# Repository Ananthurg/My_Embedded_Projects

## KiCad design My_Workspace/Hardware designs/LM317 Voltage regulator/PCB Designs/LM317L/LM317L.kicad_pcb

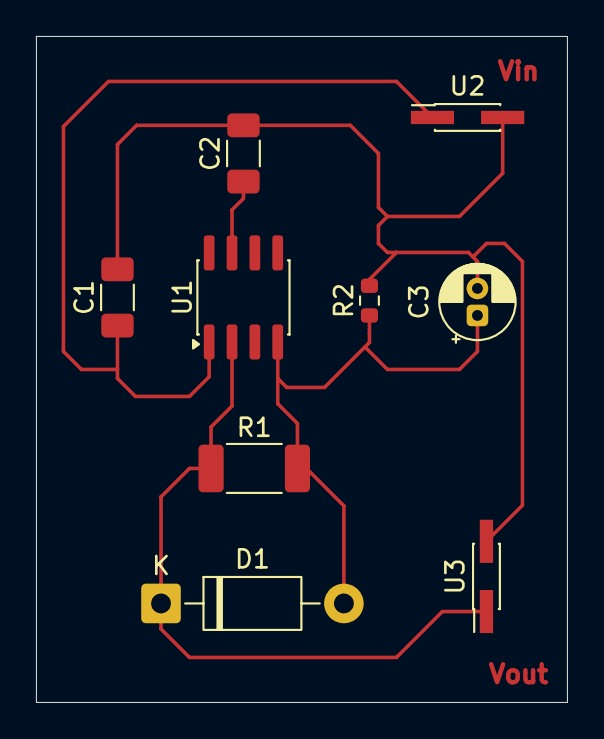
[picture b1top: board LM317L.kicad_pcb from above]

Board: 2 copper layers, 29.5 x 37.0 mm, 9 parts (0 on the bottom side), 4 nets.

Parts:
C1: 0.1uF; C_1206_3216Metric_Pad1.33x1.80mm_HandSolder
C2: 1uF; C_1206_3216Metric_Pad1.33x1.80mm_HandSolder
C3: 10uF; CP_Radial_D4.0mm_P1.50mm
D1: 1N4002; D_DO-41_SOD81_P10.16mm_Horizontal
R1: 470ohm; R_2010_5025Metric_Pad1.40x2.65mm_HandSolder
R2: 760ohm; R_0603_1608Metric
U1: LM317L_SO8; SOIC-8_3.9x4.9mm_P1.27mm
U2, U3: PinHeader_2x01_P1.27mm_Vertical_SMD

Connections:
+12V: C1.1, U1.1 (VI), U2.1
GND: C1.2, C2.2, C3.2, R2.2, U2.2, U3.2
unnamed: C3.1, D1.2 (A), R1.2, R2.1, U1.4 (ADJ)
Vout: C2.1, D1.1 (K), R1.1, U1.2 (VO), U1.3 (VO), U1.6 (VO), U1.7 (VO), U3.1
